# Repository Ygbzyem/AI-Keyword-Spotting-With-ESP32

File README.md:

# AI Speech-to-Text: Offline Keyword Spotting on ESP32

A self-designed ESP32-WROOM-32UE board listens through an INMP441 microphone, runs a 1D-CNN keyword spotter (22 classes) fully on the chip, and shows the word and confidence on an OLED. No cloud, no Wi-Fi at run time.

Report: [EN (PDF)](docs/report/CDP301_Final_Report.pdf)

## Project Structure

```
.
├── firmware/
│   ├── kws_inference/kws_inference.ino      # custom board: record 1 s -> MFE -> CNN -> OLED + LEDs
│   └── dataset_capture/dataset_capture.ino  # ESP32-S3 dev kit: stream 1 s WAV over serial
├── tools/capture_audio.py                   # PC push-to-talk recorder (hold SPACE)
├── ml/                                      # Edge Impulse settings; exported library: see edge-impulse-model/ and the Release
├── dataset/                                 # labels, recording protocol, statistics
├── hardware/                                # BOM, pin mapping, KiCad schematic and PCB
├── tests/                                   # WAV format checker, smoke test checklist
└── docs/                                    # report, figures, demo
```

## Firmware Flow

`kws_inference` is a single superloop, no RTOS tasks.

```
setup()
├── Serial 115200, LED pins (red = idle), OLED (I2C 0x3C)
├── allocate 16000 x int16 buffer, i2s_init(): 16 kHz, 32-bit frames, shift right 14 + clamp -> int16
└── on failure: OLED "Error!", all LEDs on, button ignored
loop()
└── Record button (IO34, active-low, 30 ms debounce)
    ├── yellow LED -> record_one_second(): drop 200 ms, collect 16000 samples, remove DC offset
    ├── run_classifier(): MFE + CNN
    ├── top class -> label + confidence -> OLED and serial (no rejection threshold)
    └── green LED (red or yellow if the label is "red" or "yellow") -> hold 1.5 s -> idle
```

## Component Index

| Component | Path | Role |
|---|---|---|
| Inference firmware | `firmware/kws_inference/` | On-device keyword spotting with OLED and LED output |
| Capture firmware | `firmware/dataset_capture/` | Sends one 1 s WAV per `R` command |
| Recorder | `tools/capture_audio.py` | Saves WAV clips per label |
| WAV checker | `tests/check_wav.py` | Verifies 16 kHz, 16-bit, mono, 1 s |
| Smoke test | `tests/smoke_test.md` | Manual pass/fail checklist for both boards |
| Model settings | `ml/README.md` | MFE, CNN, quantization, deployment |

## Hardware

Parts: ESP32-WROOM-32UE, INMP441, SSD1306 0.96" OLED, AMS1117-3.3, CH340C, W25Q256JVEIQ SPI flash, three LEDs, three buttons. Full list and the pin table are in [`hardware/README.md`](hardware/README.md).

| Signal | GPIO | Peripheral | Note |
|---|---|---|---|
| SD / WS / SCK | IO16 / IO17 / IO4 | INMP441 | I2S, L/R tied to GND (left) |
| SDA / SCL | IO22 / IO21 | SSD1306 | I2C, address 0x3C |
| Red / Yellow / Green | IO18 / IO5 / IO19 | Status LEDs | Idle / working / result |
| Record | IO34 | Button | Input-only, external pull-up |

## Data Flow

```
voice -> INMP441 --I2S 16 kHz--> ESP32 SRAM buffer (1 s, 16000 samples)
      -> MFE (25 ms frames, 10 ms stride, 32 Mel filters, FFT 256)  -> 3136 features
      -> 1D CNN (Conv16 -> Conv32 -> Dense128 -> 22 classes)
      -> top class + confidence -> OLED text, LED, serial log
```

## Model

22 classes (noise included): bed, bird, book, bye, cat, dog, door, eight, five, four, green, hello, nine, noise, one, red, seven, six, ten, three, two, yellow. Data was recorded with the INMP441 on an ESP32-S3 dev kit and extended with synthetic text-to-speech clips; training details and exported size are in [`ml/README.md`](ml/README.md).

## Getting Started

### Build and Flash

```bash
arduino-cli core install esp32:esp32
arduino-cli lib install "Adafruit GFX Library" "Adafruit SSD1306"

# Download AI_Keyword_Spotting.zip from the v1.0.0 Release (or export your own from Edge Impulse:
# Arduino library, EON, int8) into ml/edge-impulse-model/. SHA-256 is in ml/edge-impulse-model/README.md
arduino-cli config set library.enable_unsafe_install true
arduino-cli lib install --zip-path ml/edge-impulse-model/AI_Keyword_Spotting.zip

arduino-cli compile --fqbn esp32:esp32:esp32 firmware/kws_inference
arduino-cli upload  --fqbn esp32:esp32:esp32 -p <PORT> firmware/kws_inference
```

### Record your own data

```bash
arduino-cli compile --fqbn esp32:esp32:esp32s3 firmware/dataset_capture
arduino-cli upload  --fqbn esp32:esp32:esp32s3 -p <PORT> firmware/dataset_capture
pip install pyserial keyboard
python tools/capture_audio.py          # edit PORT and LABEL first; hold SPACE to record
python tests/check_wav.py recordings/  # verify the clips
```

Run [`tests/smoke_test.md`](tests/smoke_test.md) after flashing.

## Results

| Metric | Value | Source |
|---|---|---|
| Validation accuracy | 91.2 % (loss 0.36), 22 classes | Edge Impulse |
| Model size, int8 + EON | 136.1 KB flash, 16.8 KB RAM | Edge Impulse estimate |
| Latency, int8 | about 372 ms (MFE 361 ms + CNN 11 ms) | Edge Impulse estimate, not measured on the board |
| Demo capture | `book`, 56.6 % on the OLED | Photo in the report |

Not yet measured: on-device latency, accuracy on the physical board. Hardware files have known mismatches (LED labels, schematic vs PCB); see [`hardware/README.md`](hardware/README.md#known-discrepancies).

## Roadmap

- [ ] Measure on-device latency and accuracy with the real board
- [ ] Record the Arduino core and library versions used for the build
- [ ] Add a rejection threshold (currently the top class is always shown)
- [ ] Add a Vietnamese version of the report
- [ ] Add the demo video and the Gerber files
- [ ] Bring the KiCad schematic in line with the fabricated PCB (see hardware/README.md)

## Author

Phạm Minh Tùng, Trần Tuấn Lâm, Vũ Minh Quân, Đỗ Phước Hùng, Nguyễn Nam Khánh. CDP301, FPT University, May 2026.

## License

[MIT](LICENSE)

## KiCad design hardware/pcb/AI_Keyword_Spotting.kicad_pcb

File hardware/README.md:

# Hardware

Custom board: ESP32-WROOM-32UE, INMP441 I2S microphone, SSD1306 OLED, three status LEDs, three buttons, CH340C USB-UART, AMS1117-3.3 and a W25Q256JVEIQ SPI NOR flash. The board was designed in KiCad and submitted for the CDP301 course, so the design is frozen.

```
hardware/
├── schematic/AI_Keyword_Spotting.kicad_sch   # KiCad schematic
├── pcb/AI_Keyword_Spotting.kicad_pcb         # KiCad layout of the fabricated board
└── README.md
```

## Bill of materials (functional)

| Part | Role | Note |
|---|---|---|
| ESP32-WROOM-32UE | Main controller | 240 MHz dual core, 520 KB SRAM, external antenna connector |
| INMP441 | I2S MEMS microphone | 24-bit digital output, no external ADC |
| SSD1306 0.96" OLED | Result display | I2C, address 0x3C |
| AMS1117-3.3 | LDO regulator | 5 V USB to 3.3 V, up to 800 mA |
| CH340C | USB-to-UART bridge | Flashing and serial monitor, auto-reset via DTR/RTS transistors |
| W25Q256JVEIQ | SPI NOR flash (256 Mbit) | On its own SPI pins, see below |
| 3 x LED (red, yellow, green) | Status | Each through a 10 k resistor |
| 3 x push button | Reset, Boot, Record | 10 k pull-ups, 0.1 uF on Reset and Boot |

## Pin mapping

Signal names and GPIOs for the microphone, OLED, flash, buttons and UART come from the schematic table in the report. The LED GPIOs come from the firmware (`kws_inference.ino`), which is what runs on the board. In the demo photo of the idle state (`docs/images/10-demo-standby.jpg`) the red LED is lit while the firmware drives IO18, which agrees with the table below. The schematic names IO5 as red and IO18 as yellow, so its LED labels are swapped relative to the board as built (see Known discrepancies).

| Signal | GPIO | Peripheral | Note |
|---|---|---|---|
| SD | IO16 | INMP441 | I2S data |
| WS | IO17 | INMP441 | I2S word select |
| SCK | IO4 | INMP441 | I2S bit clock |
| L/R | GND | INMP441 | Selects the left channel |
| SCL | IO21 | SSD1306 | I2C clock |
| SDA | IO22 | SSD1306 | I2C data |
| CS | IO23 | W25Q256JVEIQ | SPI chip select |
| SCK_F | IO25 | W25Q256JVEIQ | SPI clock |
| MOSI | IO26 | W25Q256JVEIQ | |
| MISO | IO27 | W25Q256JVEIQ | |
| LED red | IO18 | Status LED | Idle / "red" result |
| LED yellow | IO5 | Status LED | Recording and recognizing / "yellow" result |
| LED green | IO19 | Status LED | Result |
| Boot | IO0 | Button | 10 k pull-up |
| Record | IO34 | Button | Input-only pin, 10 k external pull-up, active-low |
| Reset | EN | Button | 10 k pull-up |
| TXD0 / RXD0 | IO1 / IO3 | CH340C | To the PC through USB-C |

The dataset capture sketch runs on a different board, the MKE-K01 ESP32-S3 dev kit, with the microphone on WS=6, SCK=5, SD=7.

## Known discrepancies

The board was fabricated and submitted for the course, so these are documented, not changed. The PCB file describes the fabricated board; the schematic file does not match it exactly.

| # | Item | Detail |
|---|---|---|
| 1 | LED names | Schematic nets: IO5 = red, IO18 = yellow, IO19 = green. Firmware and the idle photo: IO18 = red, IO5 = yellow, IO19 = green. Use the table above. |
| 2 | Schematic vs PCB | The schematic (KiCad 10 file) has `J3` (INMP441 header) and `R6` (0 ohm) that the PCB (KiCad 9 file) does not have; the PCB has two 1x3 headers `J4` and `J5` that the schematic lacks. Do not run "Update PCB from Schematic" on these files. |
| 3 | Missing footprints | `Q1`, `Q2`, `R11` to `R14`, `C12` and `J3` have no footprint assigned in the schematic. |
| 4 | Flash part value | Schematic `U2` is labelled W25Q128JVE (128 Mbit); the part on the BOM and in the report is W25Q256JVEIQ (256 Mbit). The flash is not used by the firmware. |
| 5 | Not run | No ERC or DRC result is recorded for these files. |

## Bring-up sequence

1. Continuity and short-circuit check, then power on and measure the 3.3 V rail.
2. Flash `kws_inference` over USB-C (hold Boot, tap Reset if auto-reset does not trigger).
3. Run `tests/smoke_test.md` section B.

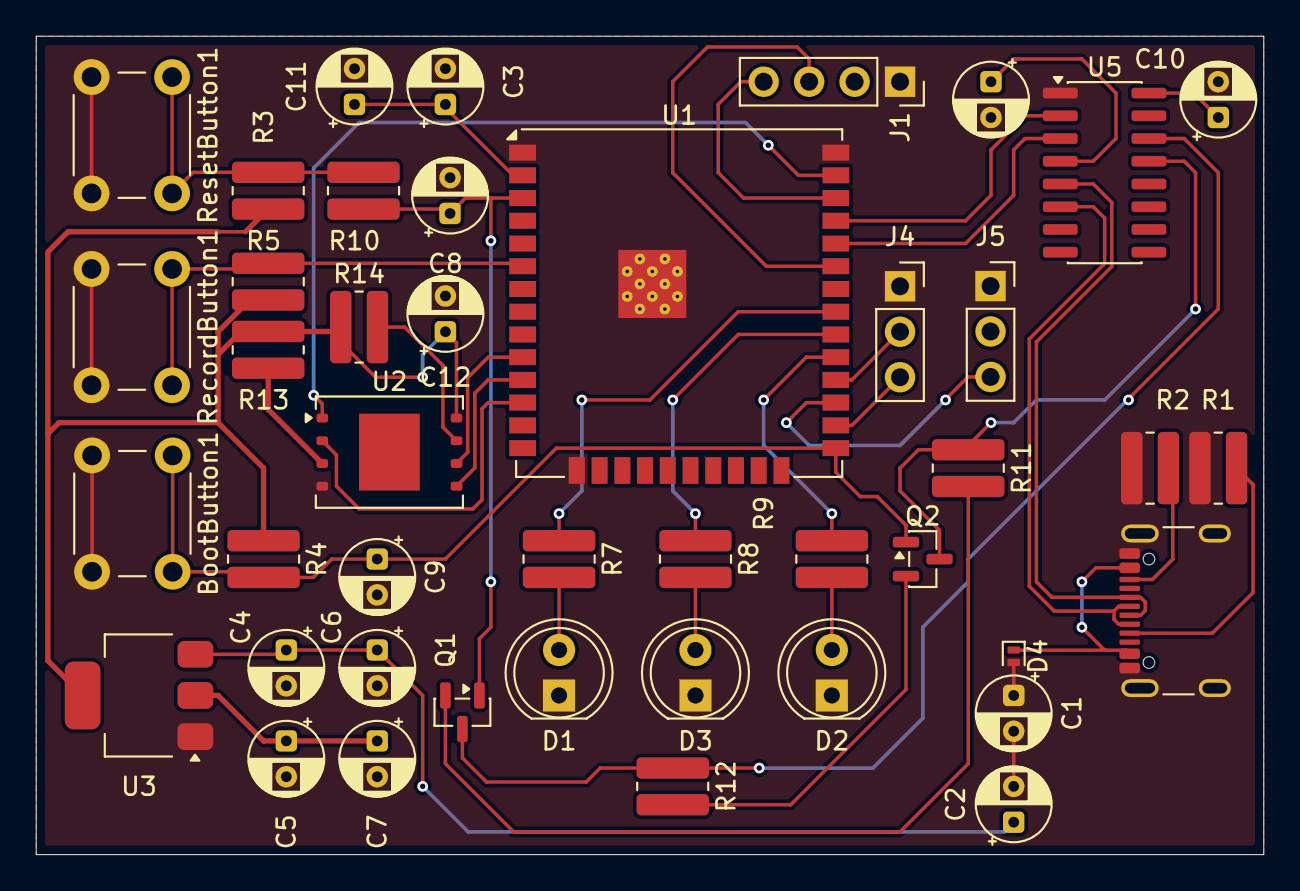
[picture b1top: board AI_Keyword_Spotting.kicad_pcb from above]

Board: 2 copper layers, 68.6 x 45.7 mm, 43 parts (0 on the bottom side), 36 nets.

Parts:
BootButton1: SW_Push; SW_PUSH_6mm
C1, C2: 4u7; CP_Radial_D4.0mm_P2.00mm
C3, C8, C9, C10, C13: 0.1uF; CP_Radial_D4.0mm_P2.00mm
C4, C5, C12: 100nF; CP_Radial_D4.0mm_P2.00mm
C6, C7: 10uF; CP_Radial_D4.0mm_P2.00mm
C11: 22uF; CP_Radial_D4.0mm_P2.00mm
D1, D2, D3: LED; LED_D5.0mm
D4: PESD5V0L1UL; D_SOD-882
J1: OLED; PinSocket_1x04_P2.54mm_Vertical
J2: USB_C_Receptacle_USB2.0_14P; USB_C_Receptacle_GCT_USB4105-xx-A_16P_TopMnt_Horizontal
J4, J5: Conn_01x03_Pin; PinSocket_1x03_P2.54mm_Vertical
Q1, Q2: NPN; SOT-23
R1, R2: 5.1k; R_0815_2038Metric_Pad1.20x4.05mm_HandSolder
R3, R4, R5, R7, R8, R9, R10, R11, R12, R13, R14: 10k; R_0815_2038Metric_Pad1.20x4.05mm_HandSolder
RecordButton1: SW_Push; SW_PUSH_6mm
ResetButton1: SW_Push; SW_PUSH_6mm
U1: ESP32-WROOM-32UE
U2: W25Q128JVE; WSON-8-1EP_8x6mm_P1.27mm_EP3.4x4.3mm
U3: AMS1117-3.3; SOT-223-3_TabPin2
U5: CH340C; SOIC-16_3.9x9.9mm_P1.27mm

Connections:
+3.3V: C3.1, C5.1, C7.1, C10.1, C11.1, C12.1, J1.2, J5.2, R3.1, R4.1, R5.1, R13.1, R14.1, U1.2 (VDD), U2.8 (VCC), U3.2 (VO), U5.16 (VCC)
+5V: C2.1, C4.1, C6.1, U3.3 (VI)
/Boot: BootButton1.1, C9.1, Q2.1 (C), R4.2, U1.25 (IO0)
/CS: U1.37 (IO23), U2.1 (~CS)
/DATA+: J2.A6 (D+), J2.B6 (D+), U5.5 (UD+)
/DATA-: J2.A7 (D-), J2.B7 (D-), U5.6 (UD-)
/DTR: Q2.3 (E), R11.1, U5.13 (~DTR)
/Green: R7.1, U1.31 (IO19)
/MISO: U1.12 (IO27), U2.2 (DO/IO_{1})
/MOSI: U1.11 (IO26), U2.5 (DI/IO_{0})
/RTS: Q1.3 (E), R12.1, U5.14 (~RTS)
/RX: U1.34 (RXD0/IO3), U5.3 (RXD)
/Record: R5.2, RecordButton1.1, U1.6 (IO34)
/Red: R9.1, U1.29 (IO5)
/Reset: C8.1, Q1.1 (C), R10.2, U1.3 (EN)
/SCK_F: U1.10 (IO25), U2.6 (CLK)
/SCK_M: J4.3, U1.26 (IO4)
/SCL: J1.3, U1.33 (IO21)
/SD: J5.3, U1.27 (IO16)
/SDA: J1.4, U1.36 (IO22)
/TX: U1.35 (TXD0/IO1), U5.2 (TXD)
/WS: J4.2, U1.28 (IO17)
/Yellow: R8.1, U1.30 (IO18)
GND: BootButton1.2, C1.1, C1.2, C2.2, C3.2, C4.2, C5.2, C6.2, C7.2, C8.2, C9.2, C10.2, C11.2, C12.2, C13.2, D1.1 (K), D2.1 (K), D3.1 (K), D4.2 (A), J1.1, J2.A1 (GND), J2.A12 (GND), J2.B1 (GND), J2.B12 (GND), J2.S1 (SHIELD), J4.1, J5.1, R1.2, R2.2, RecordButton1.2, ResetButton1.2, U1.1 (GND), U1.15 (GND), U1.38 (GND), U1.39 (GND), U2.4 (GND), U3.1 (GND), U5.1 (GND)
unnamed: D1.2 (A), R7.2
unnamed: D2.2 (A), R8.2
unnamed: D3.2 (A), R9.2
unnamed: D4.1 (K), J2.A4 (VBUS), J2.A9 (VBUS), J2.B4 (VBUS), J2.B9 (VBUS)
unnamed: J2.A5 (CC1), R1.1
unnamed: J2.B5 (CC2), R2.1
unnamed: Q1.2 (B), R11.2
unnamed: Q2.2 (B), R12.2
unnamed: R3.2, R10.1, ResetButton1.1
unnamed: R14.2, U2.7 (~HOLD/~RESET/IO_{3})
unnamed: R13.2, U2.3 (~WP/IO_{2})
unnamed: C13.1, U5.4 (V3)
